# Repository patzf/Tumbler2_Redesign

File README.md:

# Tumbler 2 `Redesign`

Corrected / upgraded version of the `HL Tumbler 2`, focused on power efficiency, signal integrity, safer power architecture and expanded connectivity.

## Overview

This redesign addresses known limitations of the original `HL Tumbler 2` across five key areas:

- Power efficiency
- Signal integrity
- Power architecture safety
- Correct GPIO input voltages
- Expandability

## Variants

To balance BOM size, cost, and feature requirements, the redesign is split into three variants, each maintained in its own branch:

| Branch           | Description                                                  | Status    |
| ---------------- | ------------------------------------------------------------ | --------- |
| `fix-only`       | Drop-in replacement using original components where possible | In Design |
| `low-cost`       | Cost-reduced BOM with two USB ports                          | In Design |
| `ultra-low-cost` | Single USB port, maximum cost reduction                      | Review    |

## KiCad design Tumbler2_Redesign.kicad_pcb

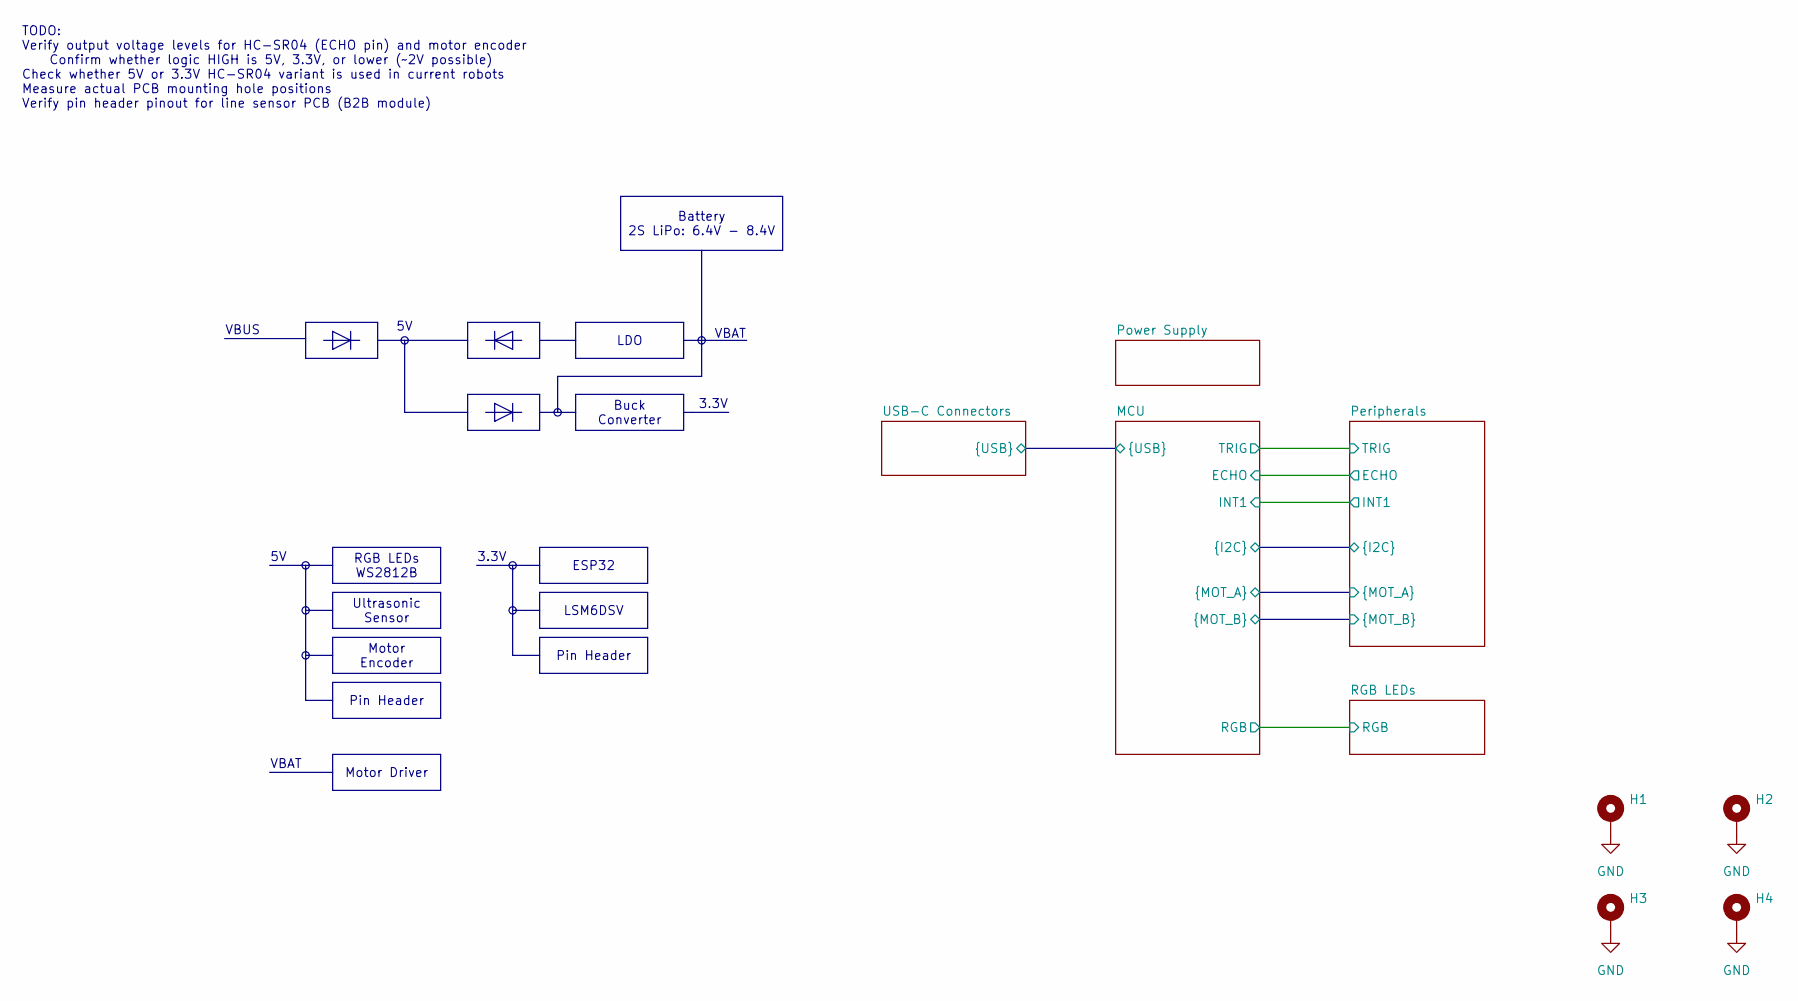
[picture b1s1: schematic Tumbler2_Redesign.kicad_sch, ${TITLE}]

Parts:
H1, H2, H3, H4: MountingHole_Pad; MountingHole_3mm_Pad_Via

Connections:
GND: H1.1, H2.1, H3.1, H4.1; also elsewhere on the board

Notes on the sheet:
TODO: Verify output voltage levels for HC-SR04 (ECHO pin) and motor encoder Confirm whether logic HIGH is 5V, 3.3V, or lower (~2V possible) Check whether 5V or 3.3V HC-SR04 variant is used in current robots Measure actual PCB mounting hole positions Verify pin header pinout for line sensor PCB (B2B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
VBUS
3.3V
VBAT
Motor Encoder
LSM6DSV
RGB LEDs WS2812B
Motor Driver
Pin Header
Buck Converter
ESP32
Battery 2S LiPo: 6.4V - 8.4V
Ultrasonic Sensor
LDO

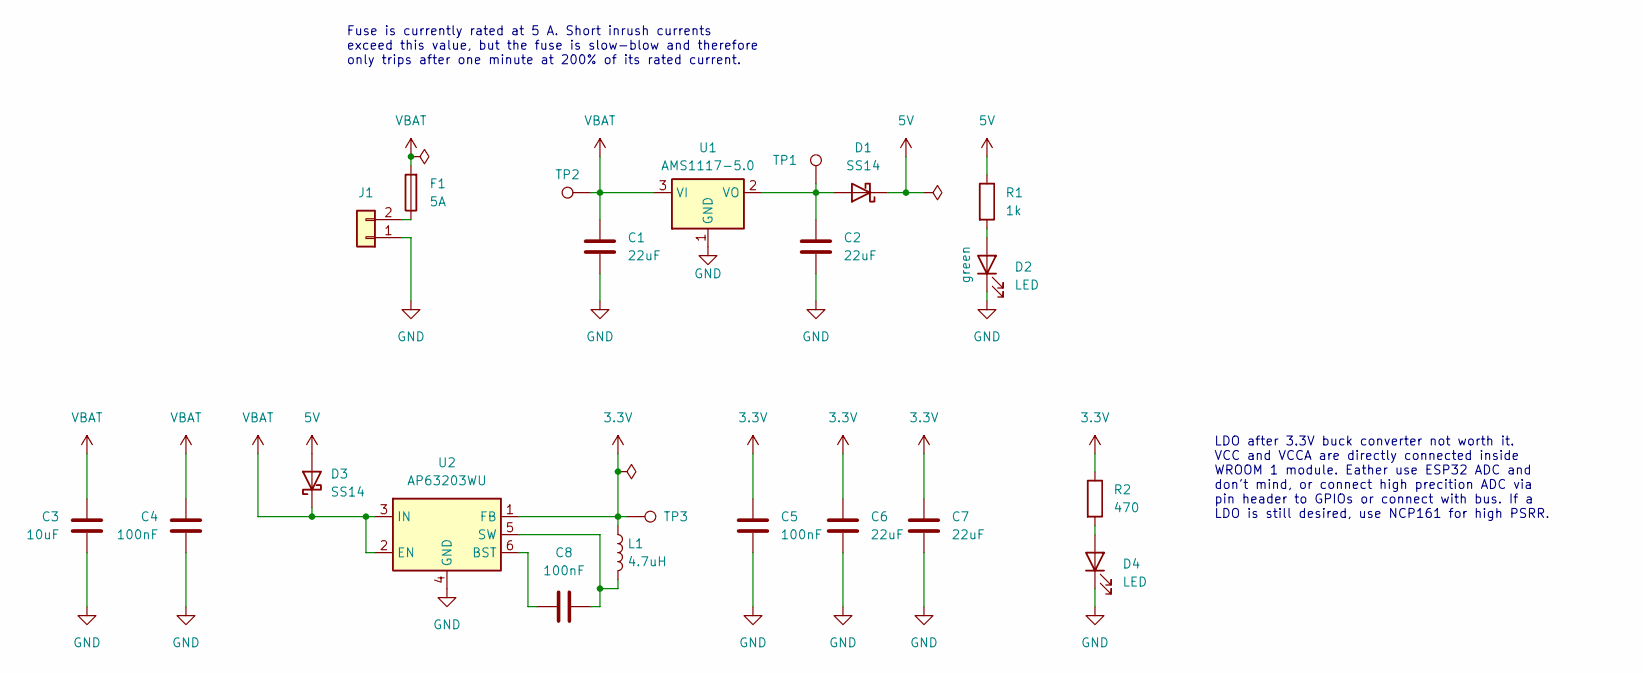
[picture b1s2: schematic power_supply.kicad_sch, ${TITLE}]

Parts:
C1, C2, C6, C7: 22uF; C_0805_2012Metric; LCSC PN C45783
C3: 10uF; C_0603_1608Metric; LCSC PN C96446
C4, C5, C8: 100nF; C_0603_1608Metric; LCSC PN C14663
D1, D3: SS14; D_SMA; LCSC PN C2480
D2, D4: LED; LED_0805_2012Metric; LCSC PN C2297
F1: 5A; Fuse_Littelfuse-NANO2-451_453; LCSC PN C66503
J1: Conn_01x02; JST_XH_S2B-XH-A-1_1x02_P2.50mm_Horizontal; LCSC PN C163035
L1: 4.7uH; VLS5045EX-4R7M; LCSC PN C307876
R1: 1k; R_0603_1608Metric; LCSC PN C21190
R2: 470; R_0603_1608Metric; LCSC PN C23179
TP1, TP2, TP3: TestPoint; TestPoint_THTPad_D1.0mm_Drill0.5mm
U1: AMS1117-5.0; SOT-223-3_TabPin2; LCSC PN C6187
U2: AP63203WU; TSOT-23-6; LCSC PN C780769

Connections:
3.3V: C5.1, C6.1, C7.1, L1.1, R2.1, TP3.1, U2.1 (FB); also elsewhere on the board
5V: D1.1 (K), D3.2 (A), R1.1; also elsewhere on the board
GND: C1.2, C2.2, C3.2, C4.2, C5.2, C6.2, C7.2, D2.1 (K), D4.1 (K), J1.1, U1.1 (GND), U2.4 (GND); also elsewhere on the board
unnamed: C2.1, D1.2 (A), TP1.1, U1.2 (VO)
unnamed: D2.2 (A), R1.2
unnamed: D4.2 (A), R2.2
unnamed: F1.1, J1.2
unnamed: C8.2, U2.6 (BST)
unnamed: C8.1, L1.2, U2.5 (SW)
VBAT: C1.1, C3.1, C4.1, D3.1 (K), F1.2, TP2.1, U1.3 (VI), U2.2 (EN), U2.3 (IN); also elsewhere on the board

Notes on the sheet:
Fuse is currently rated at 5 A. Short inrush currents exceed this value, but the fuse is slow-blow and therefore only trips after one minute at 200% of its rated current.
LDO after 3.3V buck converter not worth it. VCC and VCCA are directly connected inside WROOM 1 module. Eather use ESP32 ADC and don't mind, or connect high precition ADC via pin header to GPIOs or connect with bus. If a LDO is still desired, use NCP161 for high PSRR.

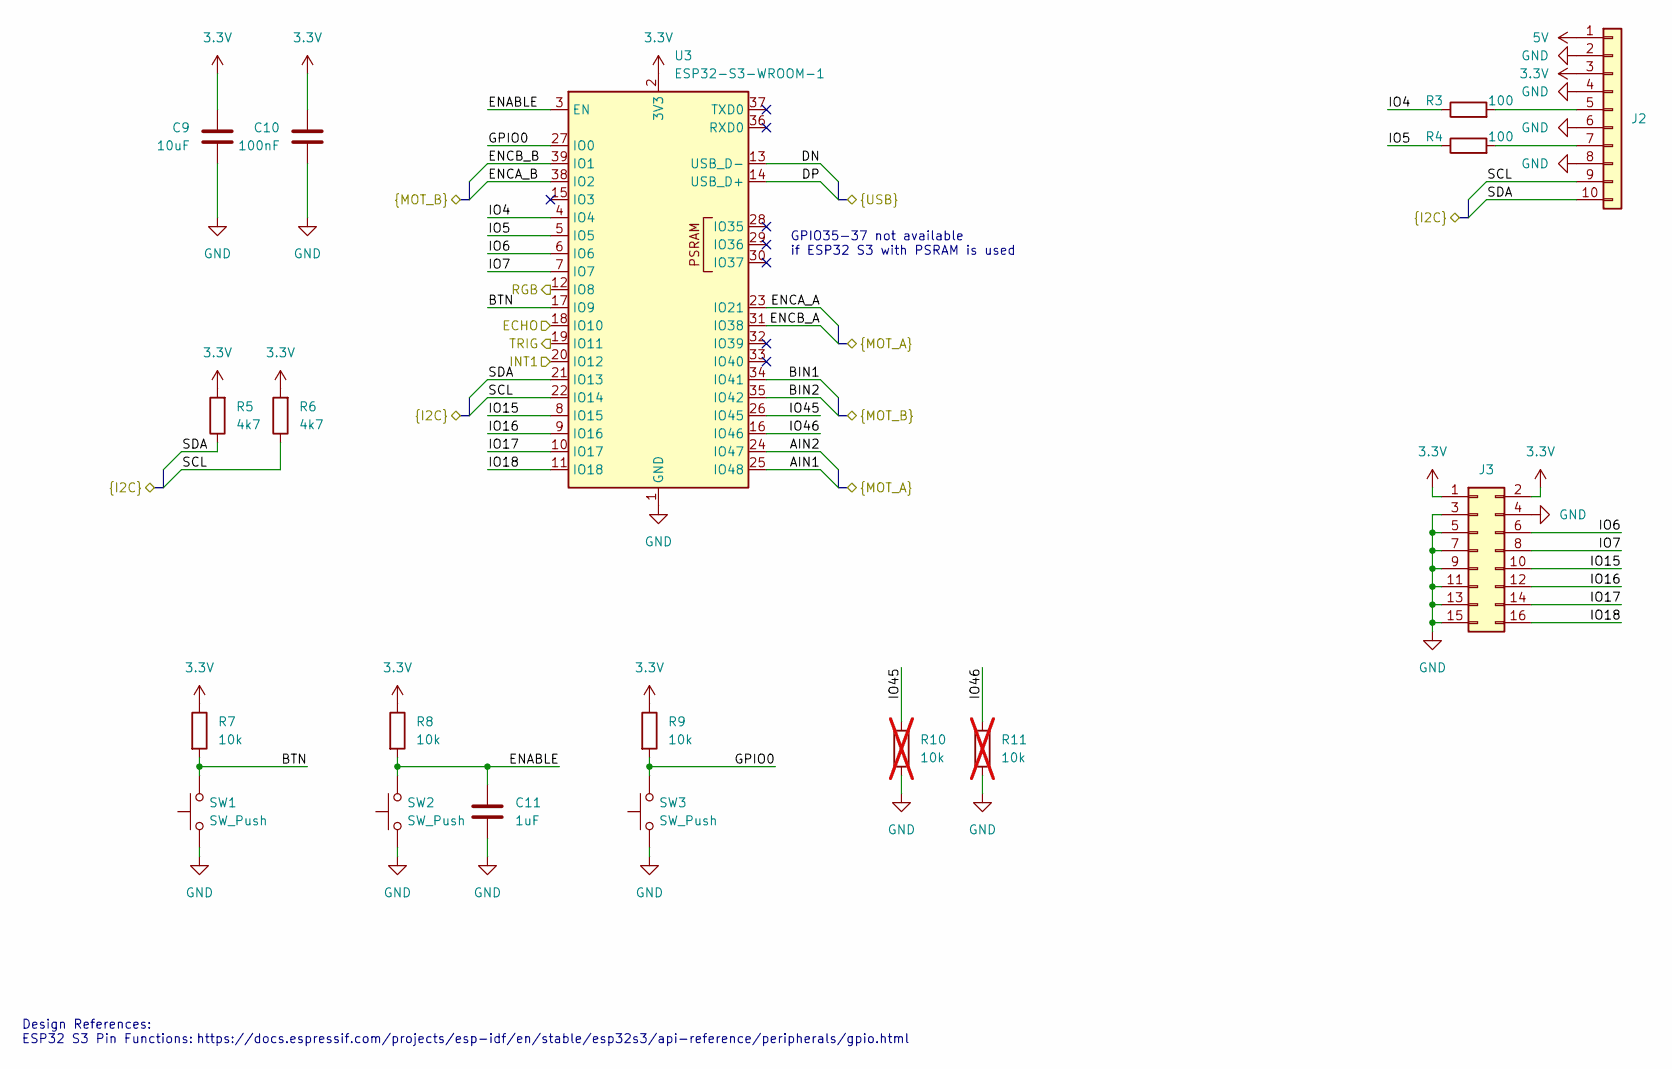
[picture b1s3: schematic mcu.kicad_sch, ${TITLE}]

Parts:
C9: 10uF; C_0603_1608Metric; LCSC PN C96446
C10: 100nF; C_0603_1608Metric; LCSC PN C14663
C11: 1uF; C_0603_1608Metric; LCSC PN C15849
J2: Conn_01x10; PinHeader_1x10_P2.54mm_Vertical
J3: Conn_02x08_Odd_Even; PinHeader_2x08_P2.54mm_Vertical
R3, R4: 100; R_0603_1608Metric; LCSC PN C22775
R5, R6: 4k7; R_0603_1608Metric; LCSC PN C23162
R7, R8, R9: 10k; R_0603_1608Metric; LCSC PN C25804
R10, R11: 10k; R_0603_1608Metric; LCSC PN C25804; not fitted
SW1, SW2, SW3: SW_Push; SW_TS-1088-AR02016; LCSC PN C720477
U3: ESP32-S3-WROOM-1; LCSC PN C2913202

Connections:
3.3V: C9.1, C10.1, J2.3, J3.1, J3.2, R5.2, R6.2, R7.1, R8.1, R9.1, U3.2 (3V3); also elsewhere on the board
5V: J2.1; also elsewhere on the board
/MCU/AIN1: U3.25 (IO48); also elsewhere on the board
/MCU/AIN2: U3.24 (IO47); also elsewhere on the board
/MCU/BIN1: U3.34 (IO41); also elsewhere on the board
/MCU/BIN2: U3.35 (IO42); also elsewhere on the board
/MCU/BTN: R7.2, SW1.2, U3.17 (IO9)
/MCU/DN: U3.13 (USB_D-); also elsewhere on the board
/MCU/DP: U3.14 (USB_D+); also elsewhere on the board
/MCU/ECHO: U3.18 (IO10); also elsewhere on the board
/MCU/ENABLE: C11.1, R8.2, SW2.2, U3.3 (EN)
/MCU/ENCA_A: U3.23 (IO21); also elsewhere on the board
/MCU/ENCA_B: U3.38 (IO2); also elsewhere on the board
/MCU/ENCB_A: U3.31 (IO38); also elsewhere on the board
/MCU/ENCB_B: U3.39 (IO1); also elsewhere on the board
/MCU/GPIO0: R9.2, SW3.2, U3.27 (IO0)
/MCU/INT1: U3.20 (IO12); also elsewhere on the board
/MCU/IO4: R3.1, U3.4 (IO4)
/MCU/IO5: R4.1, U3.5 (IO5)
/MCU/IO6: J3.6, U3.6 (IO6)
/MCU/IO7: J3.8, U3.7 (IO7)
/MCU/IO15: J3.10, U3.8 (IO15)
/MCU/IO16: J3.12, U3.9 (IO16)
/MCU/IO17: J3.14, U3.10 (IO17)
/MCU/IO18: J3.16, U3.11 (IO18)
/MCU/IO45: R10.1, U3.26 (IO45)
/MCU/IO46: R11.1, U3.16 (IO46)
/MCU/RGB: U3.12 (IO8); also elsewhere on the board
/MCU/SCL: J2.9, R6.1, U3.22 (IO14); also elsewhere on the board
/MCU/SDA: J2.10, R5.1, U3.21 (IO13); also elsewhere on the board
/MCU/TRIG: U3.19 (IO11); also elsewhere on the board
GND: C9.2, C10.2, C11.2, J2.2, J2.4, J2.6, J2.8, J3.3, J3.4, J3.5, J3.7, J3.9, J3.11, J3.13, J3.15, R10.2, R11.2, SW1.1, SW2.1, SW3.1, U3.1 (GND), U3.40 (GND), U3.41 (GND); also elsewhere on the board
unnamed: J2.5, R3.2
unnamed: J2.7, R4.2

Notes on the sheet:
GPIO35-37 not available if ESP32 S3 with PSRAM is used
Design References: ESP32 S3 Pin Functions:
https://docs.espressif.com/projects/esp-idf/en/stable/esp32s3/api-reference/peripherals/gpio.html

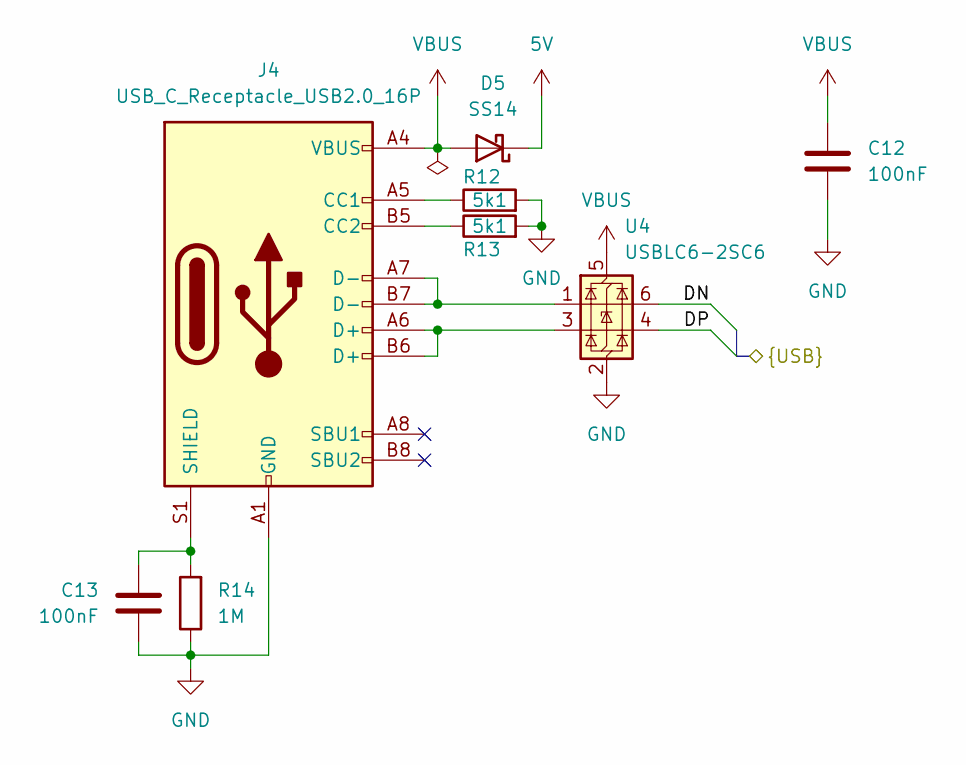
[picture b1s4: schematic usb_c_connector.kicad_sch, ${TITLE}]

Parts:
C12, C13: 100nF; C_0603_1608Metric; LCSC PN C14663
D5: SS14; D_SMA; LCSC PN C2480
J4: USB_C_Receptacle_USB2.0_16P; KINGHELM_KH-TYPE-C-16P; LCSC PN C709357
R12, R13: 5k1; R_0603_1608Metric; LCSC PN C23186
R14: 1M; R_0603_1608Metric; LCSC PN C22935
U4: USBLC6-2SC6; SOT-23-6; LCSC PN C7519

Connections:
5V: D5.1 (K); also elsewhere on the board
/MCU/DN: U4.6 (I/O1); also elsewhere on the board
/MCU/DP: U4.4 (I/O2); also elsewhere on the board
GND: C12.2, C13.2, J4.A1 (GND), J4.A12 (GND), J4.B1 (GND), J4.B12 (GND), R12.2, R13.2, R14.1, U4.2 (GND); also elsewhere on the board
unnamed: J4.A5 (CC1), R12.1
unnamed: J4.B5 (CC2), R13.1
unnamed: J4.A6 (D+), J4.B6 (D+), U4.3 (I/O2)
unnamed: J4.A7 (D-), J4.B7 (D-), U4.1 (I/O1)
unnamed: C13.1, J4.S1 (SHIELD), R14.2
VBUS: C12.1, D5.2 (A), J4.A4 (VBUS), J4.A9 (VBUS), J4.B4 (VBUS), J4.B9 (VBUS), U4.5 (VBUS)

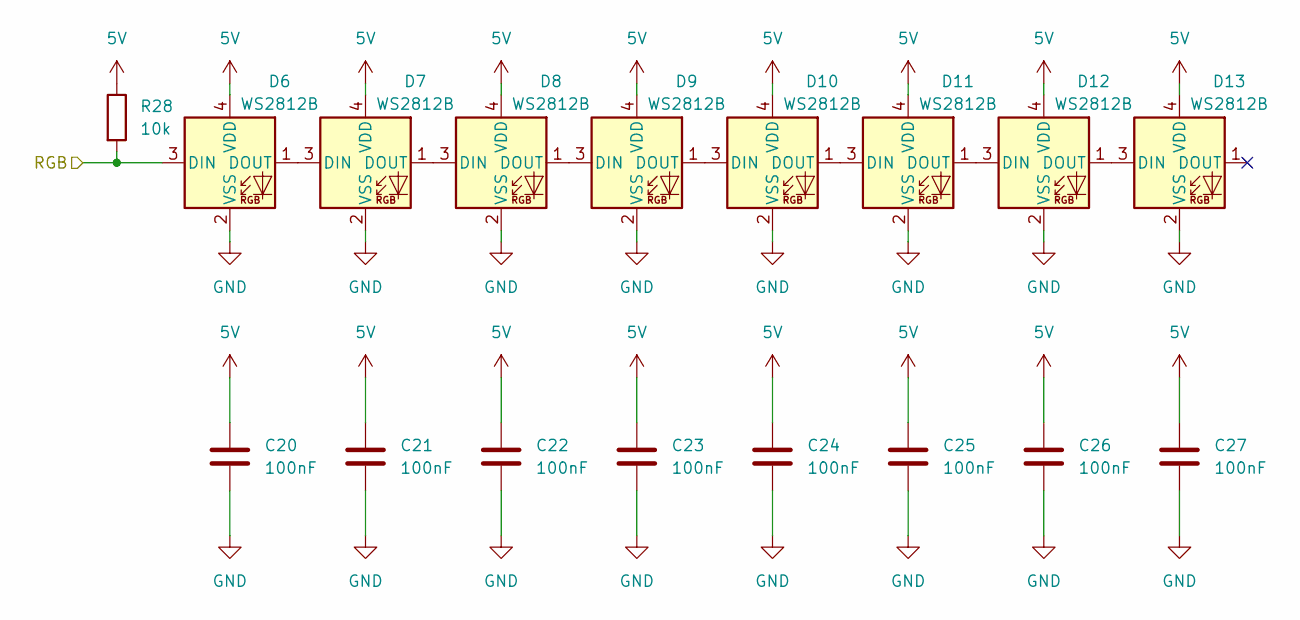
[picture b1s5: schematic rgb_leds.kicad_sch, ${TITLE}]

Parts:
C20, C21, C22, C23, C24, C25, C26, C27: 100nF; C_0603_1608Metric; LCSC PN C14663
D6, D7, D8, D9, D10, D11, D12, D13: WS2812B; LED_WS2812B-2020_PLCC4_2.0x2.0mm; LCSC PN C965555
R28: 10k; R_0603_1608Metric; LCSC PN C25804

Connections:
5V: C20.1, C21.1, C22.1, C23.1, C24.1, C25.1, C26.1, C27.1, D6.4 (VDD), D7.4 (VDD), D8.4 (VDD), D9.4 (VDD), D10.4 (VDD), D11.4 (VDD), D12.4 (VDD), D13.4 (VDD), R28.1; also elsewhere on the board
/MCU/RGB: D6.3 (DIN), R28.2; also elsewhere on the board
GND: C20.2, C21.2, C22.2, C23.2, C24.2, C25.2, C26.2, C27.2, D6.2 (VSS), D7.2 (VSS), D8.2 (VSS), D9.2 (VSS), D10.2 (VSS), D11.2 (VSS), D12.2 (VSS), D13.2 (VSS); also elsewhere on the board
unnamed: D6.1 (DOUT), D7.3 (DIN)
unnamed: D7.1 (DOUT), D8.3 (DIN)
unnamed: D8.1 (DOUT), D9.3 (DIN)
unnamed: D9.1 (DOUT), D10.3 (DIN)
unnamed: D10.1 (DOUT), D11.3 (DIN)
unnamed: D11.1 (DOUT), D12.3 (DIN)
unnamed: D12.1 (DOUT), D13.3 (DIN)

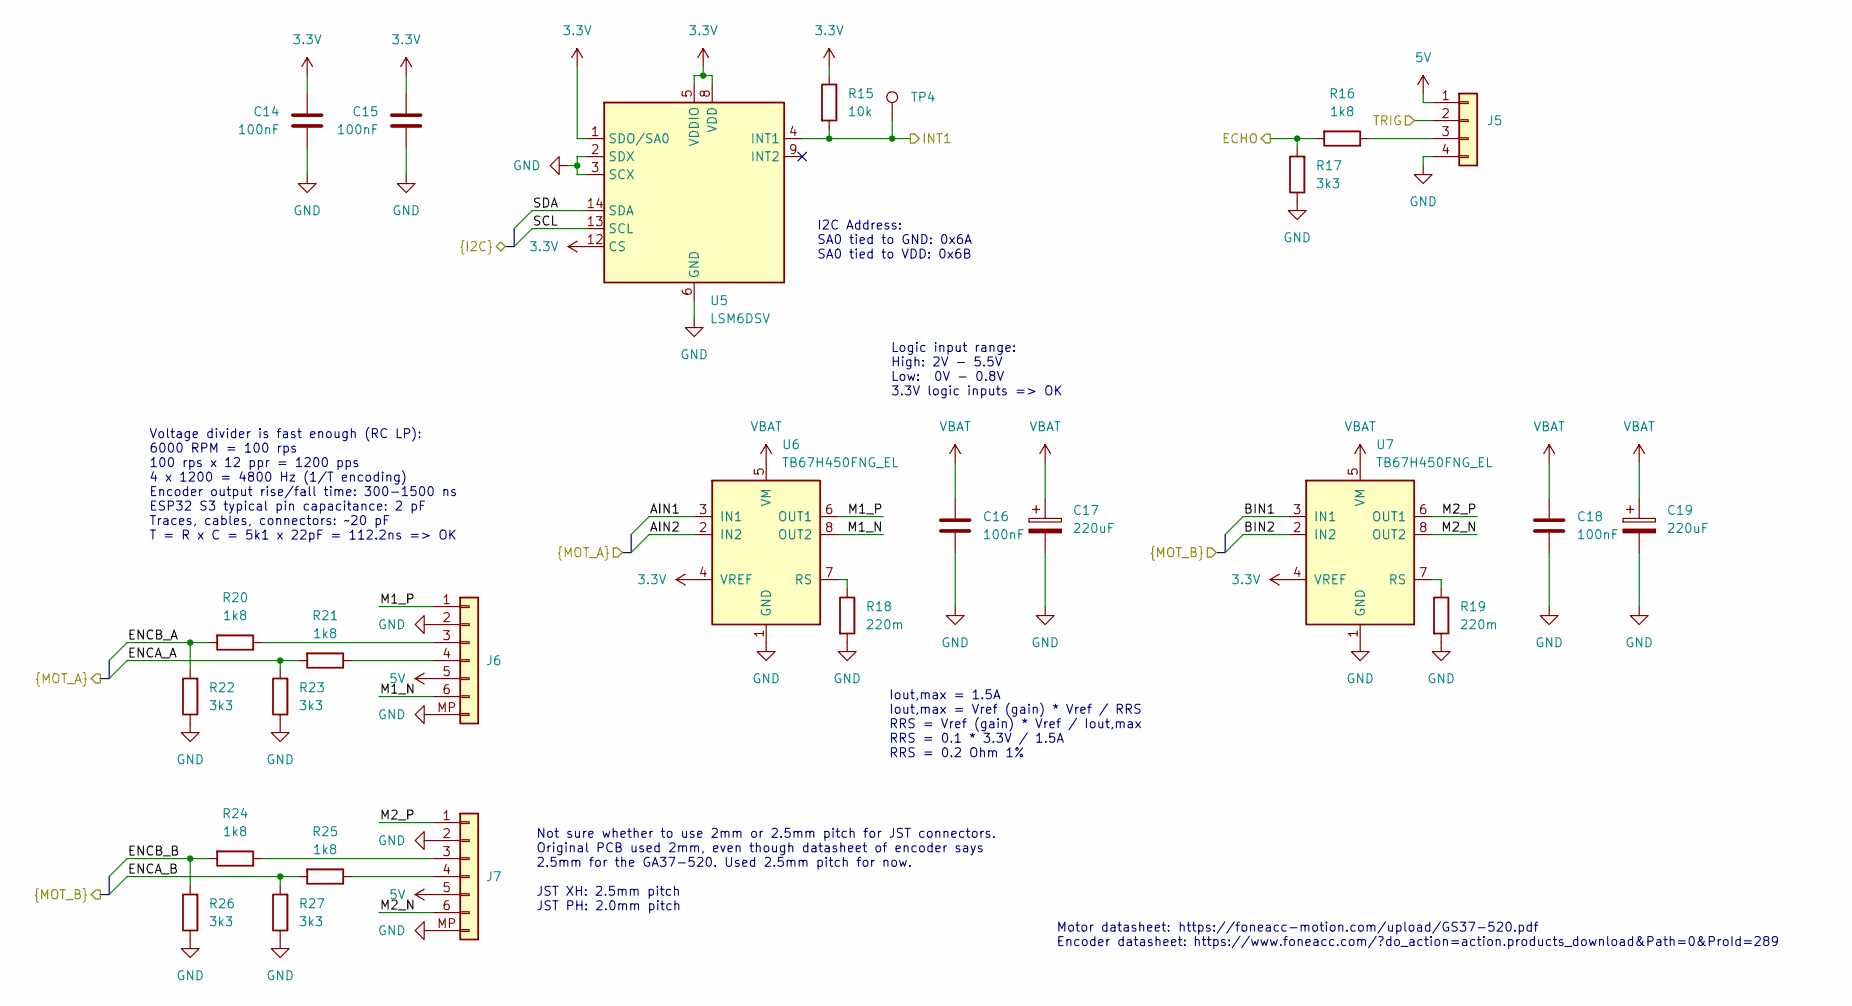
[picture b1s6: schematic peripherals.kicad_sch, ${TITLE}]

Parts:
C14, C15, C16, C18: 100nF; C_0603_1608Metric; LCSC PN C14663
C17, C19: 220uF; CP_Elec_10x10; LCSC PN C250054
J5: Conn_01x04; PinHeader_1x04_P2.54mm_Vertical; LCSC PN C5116530
J6, J7: Conn_01x06; JST_XH_S6B-XH-SM4-TB_1x06-1MP_P2.50mm_Horizontal; LCSC PN C191914
R15: 10k; R_0603_1608Metric; LCSC PN C25804
R16, R20, R21, R24, R25: 1k8; R_0603_1608Metric; LCSC PN C4177
R17, R22, R23, R26, R27: 3k3; R_0603_1608Metric; LCSC PN C22978
R18, R19: 220m; R_1210_3225Metric; LCSC PN C2934313
TP4: TestPoint; TestPoint_THTPad_D1.0mm_Drill0.5mm
U5: LSM6DSV; LGA-14_3x2.5mm_P0.5mm_LayoutBorder3x4y; LCSC PN C41785564
U6, U7: TB67H450FNG_EL; SOIC127P599X175-9N; LCSC PN C545417

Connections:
3.3V: C14.1, C15.1, R15.1, U5.1 (SDO/SA0), U5.5 (VDDIO), U5.8 (VDD), U5.12 (CS), U6.4 (VREF), U7.4 (VREF); also elsewhere on the board
5V: J5.1, J6.5, J7.5; also elsewhere on the board
/MCU/AIN1: U6.3 (IN1); also elsewhere on the board
/MCU/AIN2: U6.2 (IN2); also elsewhere on the board
/MCU/BIN1: U7.3 (IN1); also elsewhere on the board
/MCU/BIN2: U7.2 (IN2); also elsewhere on the board
/MCU/ECHO: R16.2, R17.2; also elsewhere on the board
/MCU/ENCA_A: R21.2, R23.2; also elsewhere on the board
/MCU/ENCA_B: R25.2, R27.2; also elsewhere on the board
/MCU/ENCB_A: R20.2, R22.2; also elsewhere on the board
/MCU/ENCB_B: R24.2, R26.2; also elsewhere on the board
/MCU/INT1: R15.2, TP4.1, U5.4 (INT1); also elsewhere on the board
/MCU/SCL: U5.13 (SCL); also elsewhere on the board
/MCU/SDA: U5.14 (SDA); also elsewhere on the board
/MCU/TRIG: J5.2; also elsewhere on the board
/Peripherals/M1_N: J6.6, U6.8 (OUT2)
/Peripherals/M1_P: J6.1, U6.6 (OUT1)
/Peripherals/M2_N: J7.6, U7.8 (OUT2)
/Peripherals/M2_P: J7.1, U7.6 (OUT1)
GND: C14.2, C15.2, C16.2, C17.2, C18.2, C19.2, J5.4, J6.2, J6.MP, J7.2, J7.MP, R17.1, R18.2, R19.2, R22.1, R23.1, R26.1, R27.1, U5.2 (SDX), U5.3 (SCX), U5.6 (GND), U5.7 (GND), U6.1 (GND), U6.9 (GND), U7.1 (GND), U7.9 (GND); also elsewhere on the board
unnamed: J5.3, R16.1
unnamed: J6.3, R20.1
unnamed: J6.4, R21.1
unnamed: J7.3, R24.1
unnamed: J7.4, R25.1
unnamed: R18.1, U6.7 (RS)
unnamed: R19.1, U7.7 (RS)
VBAT: C16.1, C17.1, C18.1, C19.1, U6.5 (VM), U7.5 (VM); also elsewhere on the board

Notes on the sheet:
I2C Address: SA0 tied to GND: 0x6A SA0 tied to VDD: 0x6B
Motor datasheet: Encoder datasheet:
https://foneacc-motion.com/upload/GS37-520.pdf
https://www.foneacc.com/?do_action=action.products_download&Path=0&ProId=289
Not sure whether to use 2mm or 2.5mm pitch for JST connectors. Original PCB used 2mm, even though datasheet of encoder says 2.5mm for the GA37-520. Used 2.5mm pitch for now. JST XH: 2.5mm pitch JST PH: 2.0mm pitch
Iout,max = 1.5A Iout,max = Vref (gain) * Vref / RRS RRS = Vref (gain) * Vref / Iout,max RRS = 0.1 * 3.3V / 1.5A RRS = 0.2 Ohm 1%
Voltage divider is fast enough (RC LP): 6000 RPM = 100 rps 100 rps x 12 ppr = 1200 pps 4 x 1200 = 4800 Hz (1/T encoding) Encoder output rise/fall time: 300-1500 ns ESP32 S3 typical pin capacitance: 2 pF Traces, cables, connectors: ~20 pF T = R x C = 5k1 x 22pF = 112.2ns => OK
Logic input range: High: 2V - 5.5V Low: 0V - 0.8V 3.3V logic inputs => OK

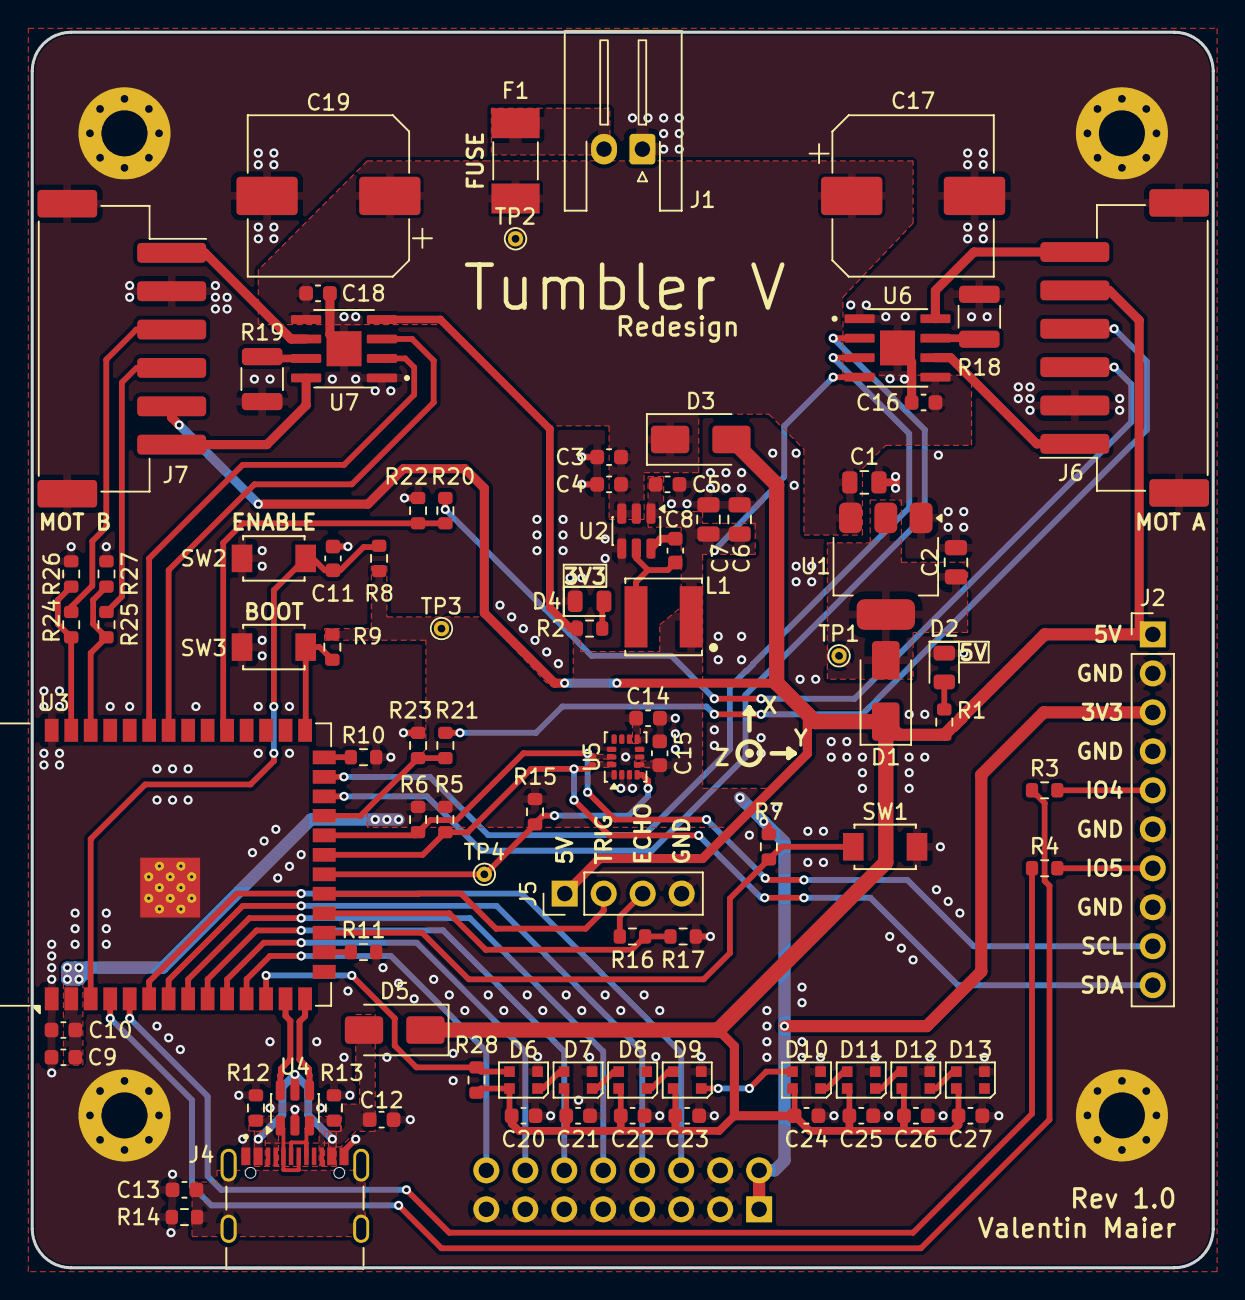
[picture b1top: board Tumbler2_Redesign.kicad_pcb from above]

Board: 2 copper layers, 77.0 x 80.5 mm, 95 parts (1 on the bottom side), 65 nets.

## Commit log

2026-02-23 Add empty KiCad project
2026-02-23 Add ESP32 and USB
2026-02-23 Add further parts
2026-02-24 Add regulators and USB to UART
2026-02-24 Remove overcurrent protection
2026-02-24 Add IMU and motor driver
2026-02-25 Move to hierarchical design
2026-02-26 Replace schottky with ideal diode
2026-02-26 Update TODO entries
2026-02-26 Follow DC-DC typical application
2026-02-26 Add test points
2026-02-26 Reset PCB and lock mounting holes
2026-03-02 Assign footprints
2026-03-02 Update LCSC symbol field
2026-03-02 Assign LCSC part numbers
2026-03-02 Add datasheet including schematics
2026-03-02 Reason about 3V3 LDO
2026-03-02 Prepare for IMU replacement
2026-03-03 Move lists to README
2026-03-03 Undo component replacement
2026-03-03 Use cheaper USB-C connector
2026-03-03 Document address assignment
2026-03-04 Connect motor driver lines
2026-03-04 Use correct connector footprint
2026-03-04 Add battery connector
2026-03-04 Fix sensor wiring
2026-03-04 Add HC-SR04 3D model
2026-03-04 Add missing pull-up for CP2102
2026-03-04 Remove caps for BTN and GPIO0
2026-03-04 Finish top level wiring
2026-03-04 Correct pin header rotation
2026-03-04 Add missing bus pull-ups
2026-03-04 Add expansion pin headers
2026-03-04 Combine peripheral modules
2026-03-05 Update pending improvements
2026-03-05 Add branch overview
2026-03-05 Correct voltage level translation
2026-03-05 Remove polyfuse as not necessary
2026-03-05 Replace polyfuse with tube fuse
2026-03-05 Break out ADC and touch pins
2026-03-05 Assign fuse clips and add fuse to BOM
2026-03-06 Move fuse to correct location
2026-03-07 Assign footprints and parts
2026-03-09 Assign inductor parts
2026-03-09 De-cascade buck converters
2026-03-09 Suggest LDO if desired
2026-03-09 Break out motor encoder signals
2026-03-09 Add test points for ultrasonic sensor
2026-03-09 Add additional bulk cap for motors
2026-03-09 Set footprint for test points
2026-03-09 Apply JLCPCB constraints
2026-03-09 Fix net connection bug
2026-03-09 Add components to layout
2026-03-09 Make lcsc field compatible with plugin
2026-03-09 Exclude test points from BOM
2026-03-09 Add missing rgb leds
2026-03-09 Add power rail block diagram
2026-03-10 Replace with cheaper components
2026-03-10 Replace IMU with modern alternative
2026-03-10 Remove unused symbol field
2026-03-10 Use basic parts where possible
2026-03-10 Group components
2026-03-11 Sketch out component placement
2026-03-11 Fix bus merging and add net classes
2026-03-12 Start conceptual layouting
2026-03-16 Continue layout and update schematic
2026-03-17 Continue layout and add pin header protection
2026-03-18 Add linesensor pin header
2026-03-19 Document strapping pins
2026-03-19 Add layout options
2026-03-19 Update layout option captions
2026-03-20 Change purpose of main branch
2026-03-20 Update design changes
2026-03-24 Connect remaining tracks
2026-03-24 Solve some DRC errors and warnings
2026-03-24 Prepare for fabrication
2026-03-24 Update branch status
2026-03-24 Add todo list and update block diagram
2026-03-28 cleanup schemati, replaced some caps from 0603 to 0805 around Linear Regulator
